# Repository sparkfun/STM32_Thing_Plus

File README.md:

SparkFun STM32 Thing Plus
========================================

[*SparkFun STM32 Thing Plus (17712)*](https://www.sparkfun.com/products/17712)

What incorporates a high-performance Arm® Cortex®-M4 32-bit RISC core, a full set of DSP instructions, memory protection unit (MPU), high-speed embedded memories, up to 4 Kbytes of backup SRAM, and an extensive range of enhanced I/Os and peripherals? The new [SparkFun STM32 Thing Plus](https://www.sparkfun.com/products/17712) has all this and more in the popular, Feather-compatible Thing Plus form factor. 

Repository Contents
-------------------

* **/Hardware** - Eagle design files (.brd, .sch)
* **/Production** - Production panel files (.brd)

Documentation
--------------
* **[Hookup Guide](https://learn.sparkfun.com/tutorials/stm32-thing-plus-hookup-guide)** - Basic hookup guide for the STM32 Thing Plus.
* **[SparkFun Graphical Datasheets](https://github.com/sparkfun/Graphical_Datasheets)** -Graphical Datasheets for various SparkFun products.

License Information
-------------------

This product is _**open source**_! 

Please review the LICENSE.md file for license information. 

If you have any questions or concerns on licensing, please contact technical support on our [SparkFun forums](https://forum.sparkfun.com/viewforum.php?f=152).

Distributed as-is; no warranty is given.

- Your friends at SparkFun.

_<COLLABORATION CREDIT>_

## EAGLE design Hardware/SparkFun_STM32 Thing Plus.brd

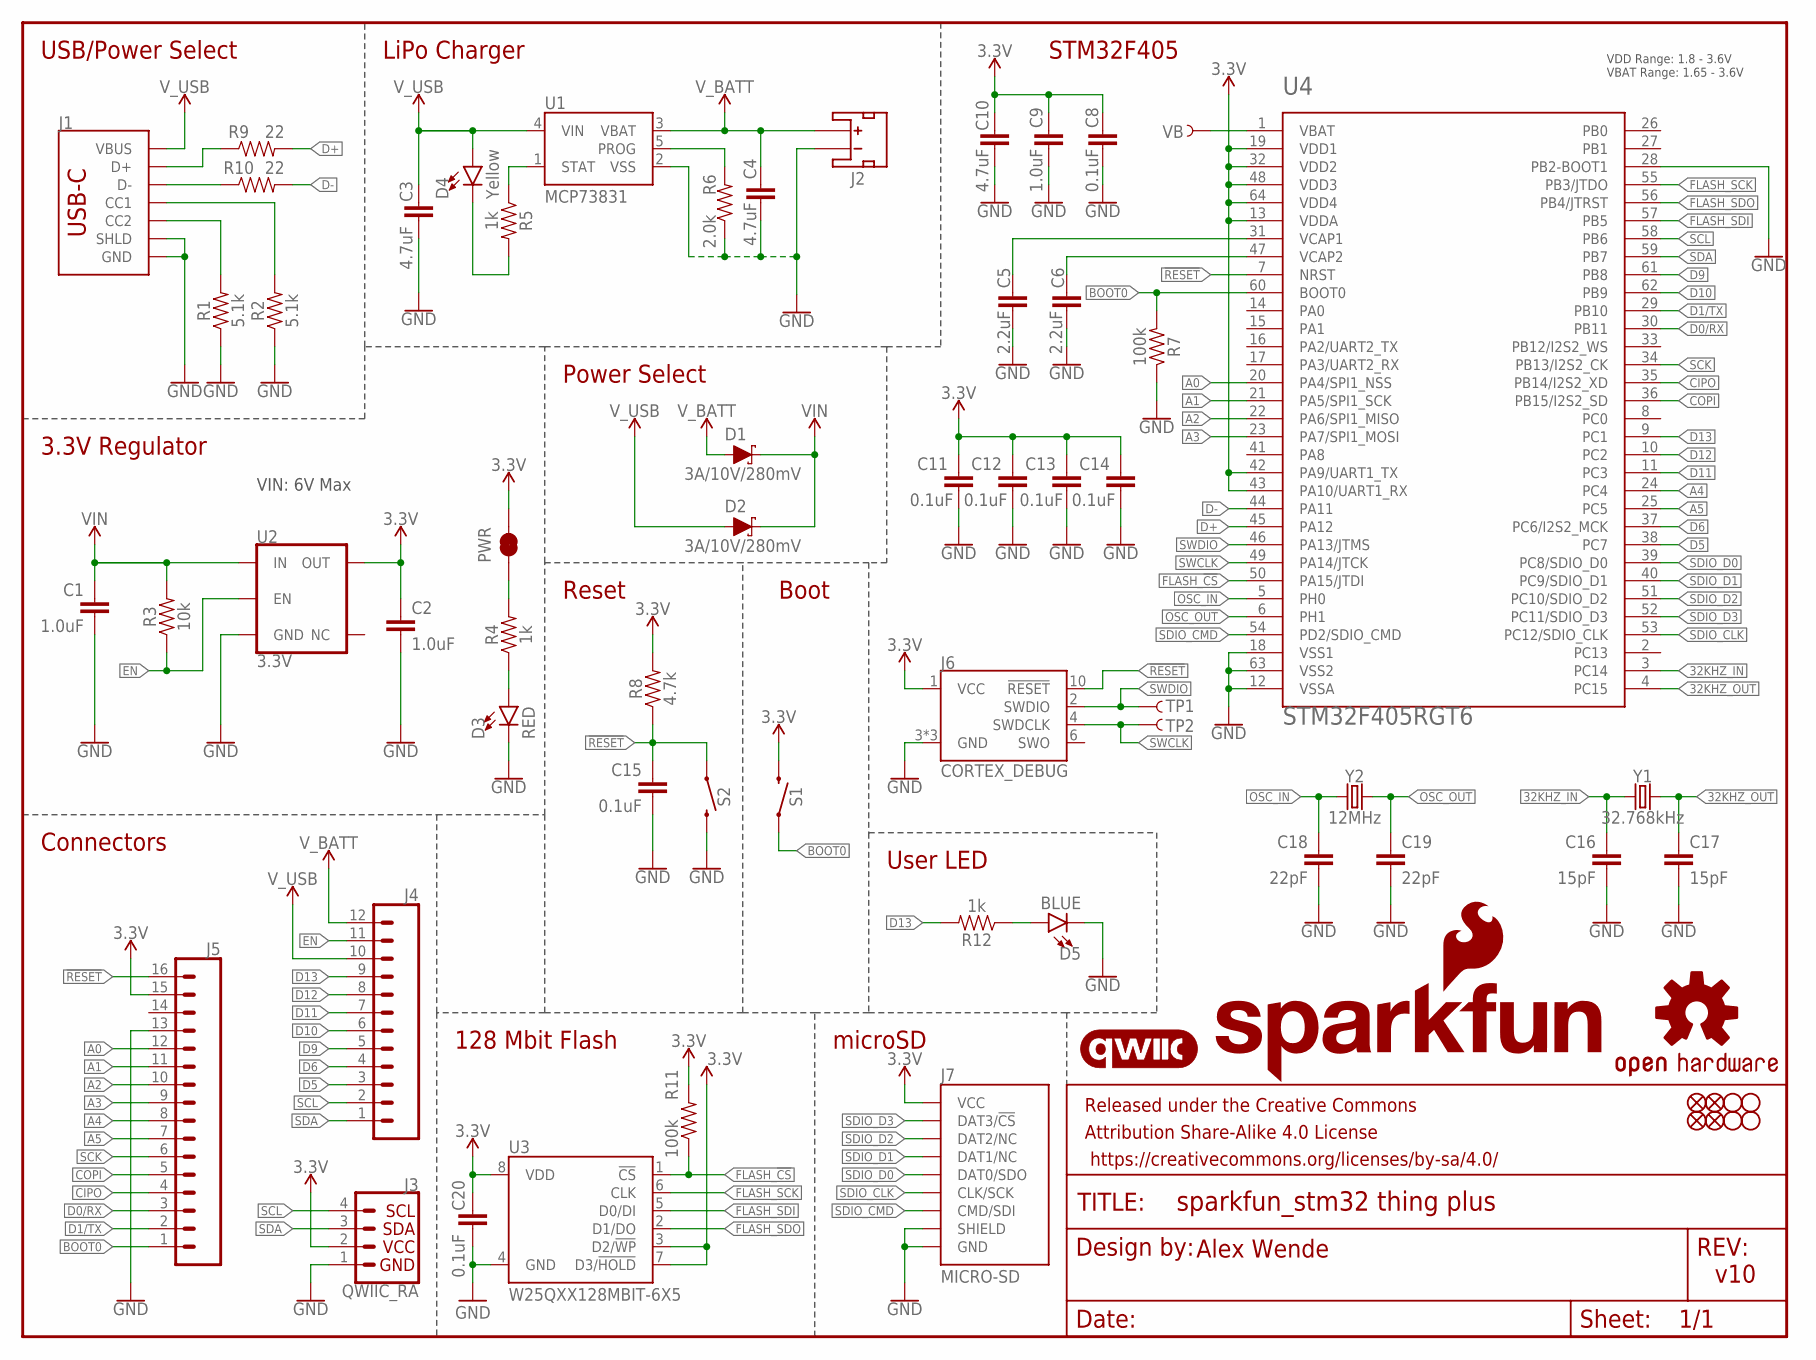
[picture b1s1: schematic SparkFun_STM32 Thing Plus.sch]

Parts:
C1, C2, C9: 1.0uF; 0402-TIGHT
C3, C4, C10: 4.7uF; 0402-TIGHT
C5, C6: 2.2uF; 0402-TIGHT
C8, C11, C12, C13, C14, C15, C20: 0.1uF; 0402-TIGHT
C16, C17: 15pF; 0402-TIGHT
C18, C19: 22pF; 0402-TIGHT
D1, D2: 3A/10V/280mV; SOD-323
D3: RED; LED-0603
D4: Yellow; LED-0603
D5: BLUE; LED-0603
FD1, FD2, FD3, FD4: FIDUCIALUFIDUCIAL; FIDUCIAL-MICRO
FRAME1: FRAME-LETTER; CREATIVE_COMMONS
H1, H2, H3, H4: STAND-OFFTIGHT; STAND-OFF-TIGHT
J1: USB_C_2-LAYER_PADS; USB-C-16P-2LAYER-PADS
J2: JST_2MM_MALE; JST-2-SMD
J3: QWIIC_RA; JST04_1MM_RA
J4: CONN_12SM_SQ_NO_SILK; 1X12_SM_SQ_NOSILK
J5: CONN_161X16_SM_SQ_NOSILK; 1X16_SM_SQ_NOSILK
J6: CORTEX_DEBUG; 2X5-PTH-1.27MM-NO_SILK
J7: MICRO-SD; MICRO-SD-SOCKET
LOGO1: QWIIC_LOGO_5MM; QWIIC_5MM
LOGO2: SFE_LOGO_NAME_FLAME.1_INCH; SFE_LOGO_NAME_FLAME_.1
LOGO3: OSHW-LOGOS; OSHW-LOGO-S
PWR: JUMPER-SMT_2_NC_TRACE_NO-SILK; SMT-JUMPER_2_NC_TRACE_NO-SILK
R1, R2: 5.1k; 0603
R3: 10k; 0603
R4, R5, R12: 1k; 0402-TIGHT
R6: 2.0k; 0603
R7, R11: 100k; 0402-TIGHT
R8: 4.7k; 0603
R9, R10: 22; 0603
S1, S2: MOMENTARY-SWITCH-SPST-SMD-4.6X2.8MM; TACTILE_SWITCH_SMD_4.6X2.8MM
TP1, TP2: TEST-POINT3; PAD.03X.03
U1: MCP73831; SOT23-5
U2: 3.3V; SOT23-5
U3: W25QXX128MBIT-6X5; WSON-8-6X5
U4: STM32F405RGT6; TQFP64
VB: TEST-POINT3; PAD.03X.03
Y1: 32.768kHz; CRYSTAL-SMD-3.2X1.5MM
Y2: 12MHz; CRYSTAL-SMD-5X3.2-4PAD

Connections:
3.3V: C2.1, C8.1, C9.1, C10.1, C11.1, C12.1, C13.1, C14.1, C20.1, J3.2, J5.15, J6.1 (VCC), J7.VCC, PWR.2, R8.2, R11.2, S1.3 (2), S1.4 (2), U2.5 (OUT), U3.3 (D2/!WP!), U3.7 (D3/!HOLD!), U3.8 (VDD), U4.13 (VDDA), U4.19 (VDD1), U4.32 (VDD2), U4.42 (PA9/UART1_TX), U4.43 (PA10/UART1_RX), U4.48 (VDD3), U4.64 (VDD4)
32KHZ_IN: C16.1, U4.3 (PC14), Y1.P$1 (1)
32KHZ_OUT: C17.1, U4.4 (PC15), Y1.P$2 (2)
!RESET: C15.1, J5.16, J6.10 (!RESET), R8.1, S2.1, S2.2 (1), U4.7 (NRST)
A0: J5.12, U4.20 (PA4/SPI1_NSS)
A1: J5.11, U4.21 (PA5/SPI1_SCK)
A2: J5.10, U4.22 (PA6/SPI1_MISO)
A3: J5.9, U4.23 (PA7/SPI1_MOSI)
A4: J5.8, U4.24 (PC4)
A5: J5.7, U4.25 (PC5)
BOOT0: J5.1, R7.2, S1.1, S1.2 (1), U4.60 (BOOT0)
CIPO: J5.4, U4.35 (PB14/I2S2_XD)
COPI: J5.5, U4.36 (PB15/I2S2_SD)
D0/RX: J5.3, U4.30 (PB11)
D1/TX: J5.2, U4.29 (PB10)
D5: J4.3, U4.38 (PC7)
D6: J4.4, U4.37 (PC6/I2S2_MCK)
D9: J4.5, U4.61 (PB8)
D10: J4.6, U4.62 (PB9)
D11: J4.7, U4.11 (PC3)
D12: J4.8, U4.10 (PC2)
D13: J4.9, R12.2, U4.9 (PC1)
D+: R9.2, U4.45 (PA12)
D-: R10.2, U4.44 (PA11)
EN: J4.11, R3.1, U2.3 (EN)
FLASH_!CS: R11.1, U3.1 (!CS!), U4.50 (PA15/JTDI)
FLASH_SCK: U3.6 (CLK), U4.55 (PB3/JTDO)
FLASH_SDI: U3.5 (D0/DI), U4.57 (PB5)
FLASH_SDO: U3.2 (D1/DO), U4.56 (PB4/JTRST)
GND: C1.2, C2.2, C3.2, C4.2, C5.2, C6.2, C8.2, C9.2, C10.2, C11.2, C12.2, C13.2, C14.2, C15.2, C16.2, C17.2, C18.2, C19.2, C20.2, D3.C, D5.C, J1.GND, J1.GND2 (GND), J1.SHLD1 (SHLD), J1.SHLD2 (SHLD), J1.SHLD3 (SHLD), J1.SHLD4 (SHLD), J2.1 (-), J3.1, J5.13, J6.3 (GND), J6.5 (GND), J6.9 (GND), J7.CD1 (SHIELD), J7.GND, J7.GND1 (GND), J7.GND3 (GND), R1.1, R2.1, R6.1, R7.1, S2.3 (2), S2.4 (2), U1.2 (VSS), U2.2 (GND), U3.4 (GND), U4.12 (VSSA), U4.18 (VSS1), U4.28 (PB2-BOOT1), U4.63 (VSS2)
unnamed: D5.A, R12.1
unnamed: PWR.1, R4.2
unnamed: J1.A6 (D+), J1.B6 (D+), R9.1
unnamed: J1.A7 (D-), J1.B7 (D-), R10.1
unnamed: D3.A, R4.1
unnamed: R6.2, U1.5 (PROG)
unnamed: J1.A5 (CC1), R2.2
unnamed: J1.B5 (CC2), R1.2
unnamed: D4.C, R5.2
unnamed: R5.1, U1.1 (STAT)
unnamed: C5.1, U4.31 (VCAP1)
unnamed: C6.1, U4.47 (VCAP2)
OSC_IN: C18.1, U4.5 (PH0), Y2.1
OSC_OUT: C19.1, U4.6 (PH1), Y2.3 (2)
SCK: J5.6, U4.34 (PB13/I2S2_CK)
SCL: J3.4, J4.2, U4.58 (PB6)
SDA: J3.3, J4.1, U4.59 (PB7)
SDIO_CLK: J7.SCLK (CLK/SCK), U4.53 (PC12/SDIO_CLK)
SDIO_CMD: J7.DI/CMD (CMD/SDI), U4.54 (PD2/SDIO_CMD)
SDIO_D0: J7.DO/DAT0 (DAT0/SDO), U4.39 (PC8/SDIO_D0)
SDIO_D1: J7.DAT1 (DAT1/NC), U4.40 (PC9/SDIO_D1)
SDIO_D2: J7.DAT2 (DAT2/NC), U4.51 (PC10/SDIO_D2)
SDIO_D3: J7.CS/DAT3 (DAT3/!CS!), U4.52 (PC11/SDIO_D3)
SWCLK: J6.4 (SWDCLK), TP2.P$1, U4.49 (PA14/JTCK)
SWDIO: J6.2 (SWDIO), TP1.P$1, U4.46 (PA13/JTMS)
VB: U4.1 (VBAT), VB.P$1
VIN: C1.1, D1.C, D2.C, R3.2, U2.1 (IN)
V_BATT: C4.1, D1.A, J2.2 (+), J4.12, U1.3 (VBAT)
V_USB: C3.1, D2.A, D4.A, J1.VBUS1 (VBUS), J1.VBUS2 (VBUS), J4.10, U1.4 (VIN)

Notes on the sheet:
v10
Alex Wende
3.3V Regulator
VIN: 6V Max
LiPo Charger
USB/Power Select
Power Select
Connectors
microSD
128 Mbit Flash
Reset
Boot
User LED
VDD Range: 1.8 - 3.6V VBAT Range: 1.65 - 3.6V
STM32F405

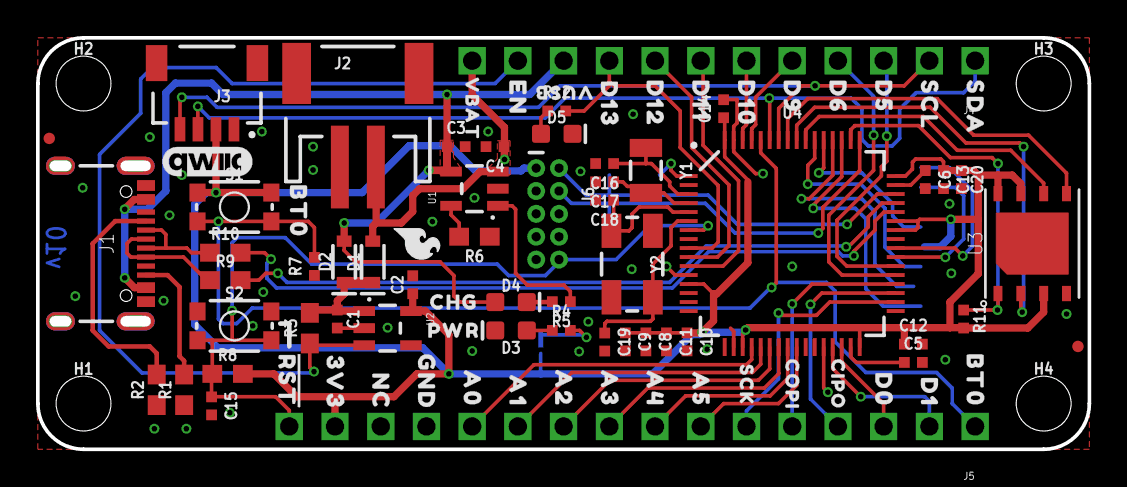
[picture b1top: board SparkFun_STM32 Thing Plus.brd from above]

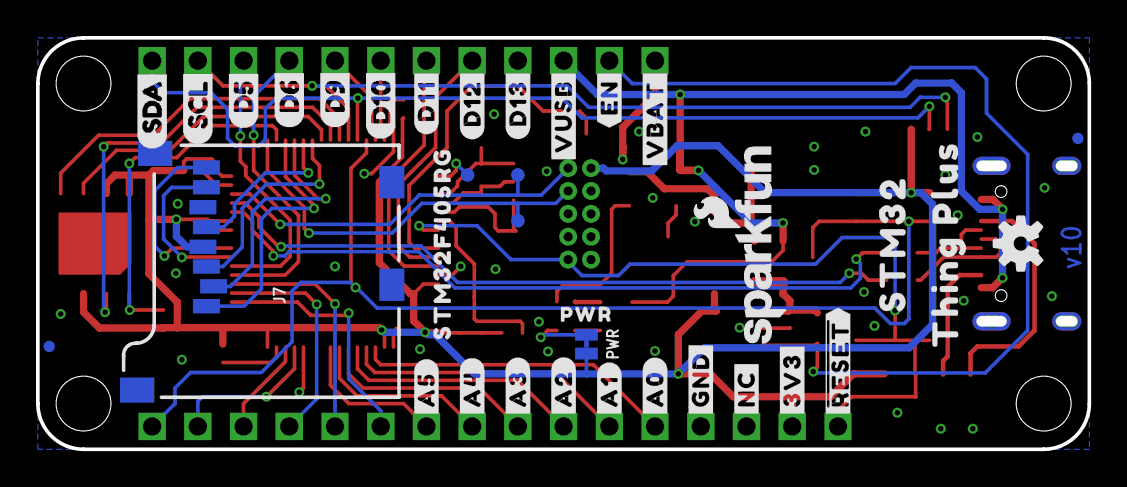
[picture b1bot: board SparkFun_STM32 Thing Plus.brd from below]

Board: 2 copper layers, 58.4 x 22.9 mm, 125 parts (35 on the bottom side), 59 nets.

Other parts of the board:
U$1: D53
U$2: #RST#0
U$3, U$49: BT00
U$4: D130
U$5, U$58: PWR0
U$6: CHG0
U$7: ##RESET##0
U$8: #3V3#0
U$9: #NC#0
U$10: #GND#0
U$11: #A0#0
U$12: #A1#0
U$13: #A2#0
U$14: #A3#0
U$15: #A4#0
U$16: #A5#0
U$23: D62
U$24: D91
U$25, U$55: D100
U$26: SCL4
U$27: SDA5
U$29: #D11#0
U$30: #D12#0
U$31: #D13#0
U$32: #VUSB#0
U$33: #EN#0
U$34: #VBAT#0
U$35: 3V30
U$36: NC0
U$37: GND0
U$38: A00
U$39: A10
U$40: A20
U$41: A30
U$42: A40
U$43: A50
U$44: SCK0
U$45: COPI0
U$46: CIPO0
U$47: D00
U$48: D10
U$50: VBAT_0
U$51: EN_0
U$52: D50
U$53: D60
U$54: D90
U$56: D110
U$57: D120
U$59: SCL_0
U$60: SDA_0
U$61: VUSB0
U$62: STM320
U$63: THING_PLUS0
U$64: STM32F405RG0
U$65: SFE_LOGO_FLAME_.1

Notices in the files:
parts and their libraries:
SparkFun-Capacitors: Licensing: Creative Commons ShareAlike 4.0 International - https://creativecommons.org/licenses/by-sa/4.0
SparkFun-Aesthetics: Released under the Creative Commons Attribution Share-Alike 4.0 License
SparkFun-Aesthetics: https://creativecommons.org/licenses/by-sa/4.0
